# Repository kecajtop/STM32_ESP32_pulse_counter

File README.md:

# STM32_ESP32_pulse_counter

ESP32-S2-WROVER-I-N4R2

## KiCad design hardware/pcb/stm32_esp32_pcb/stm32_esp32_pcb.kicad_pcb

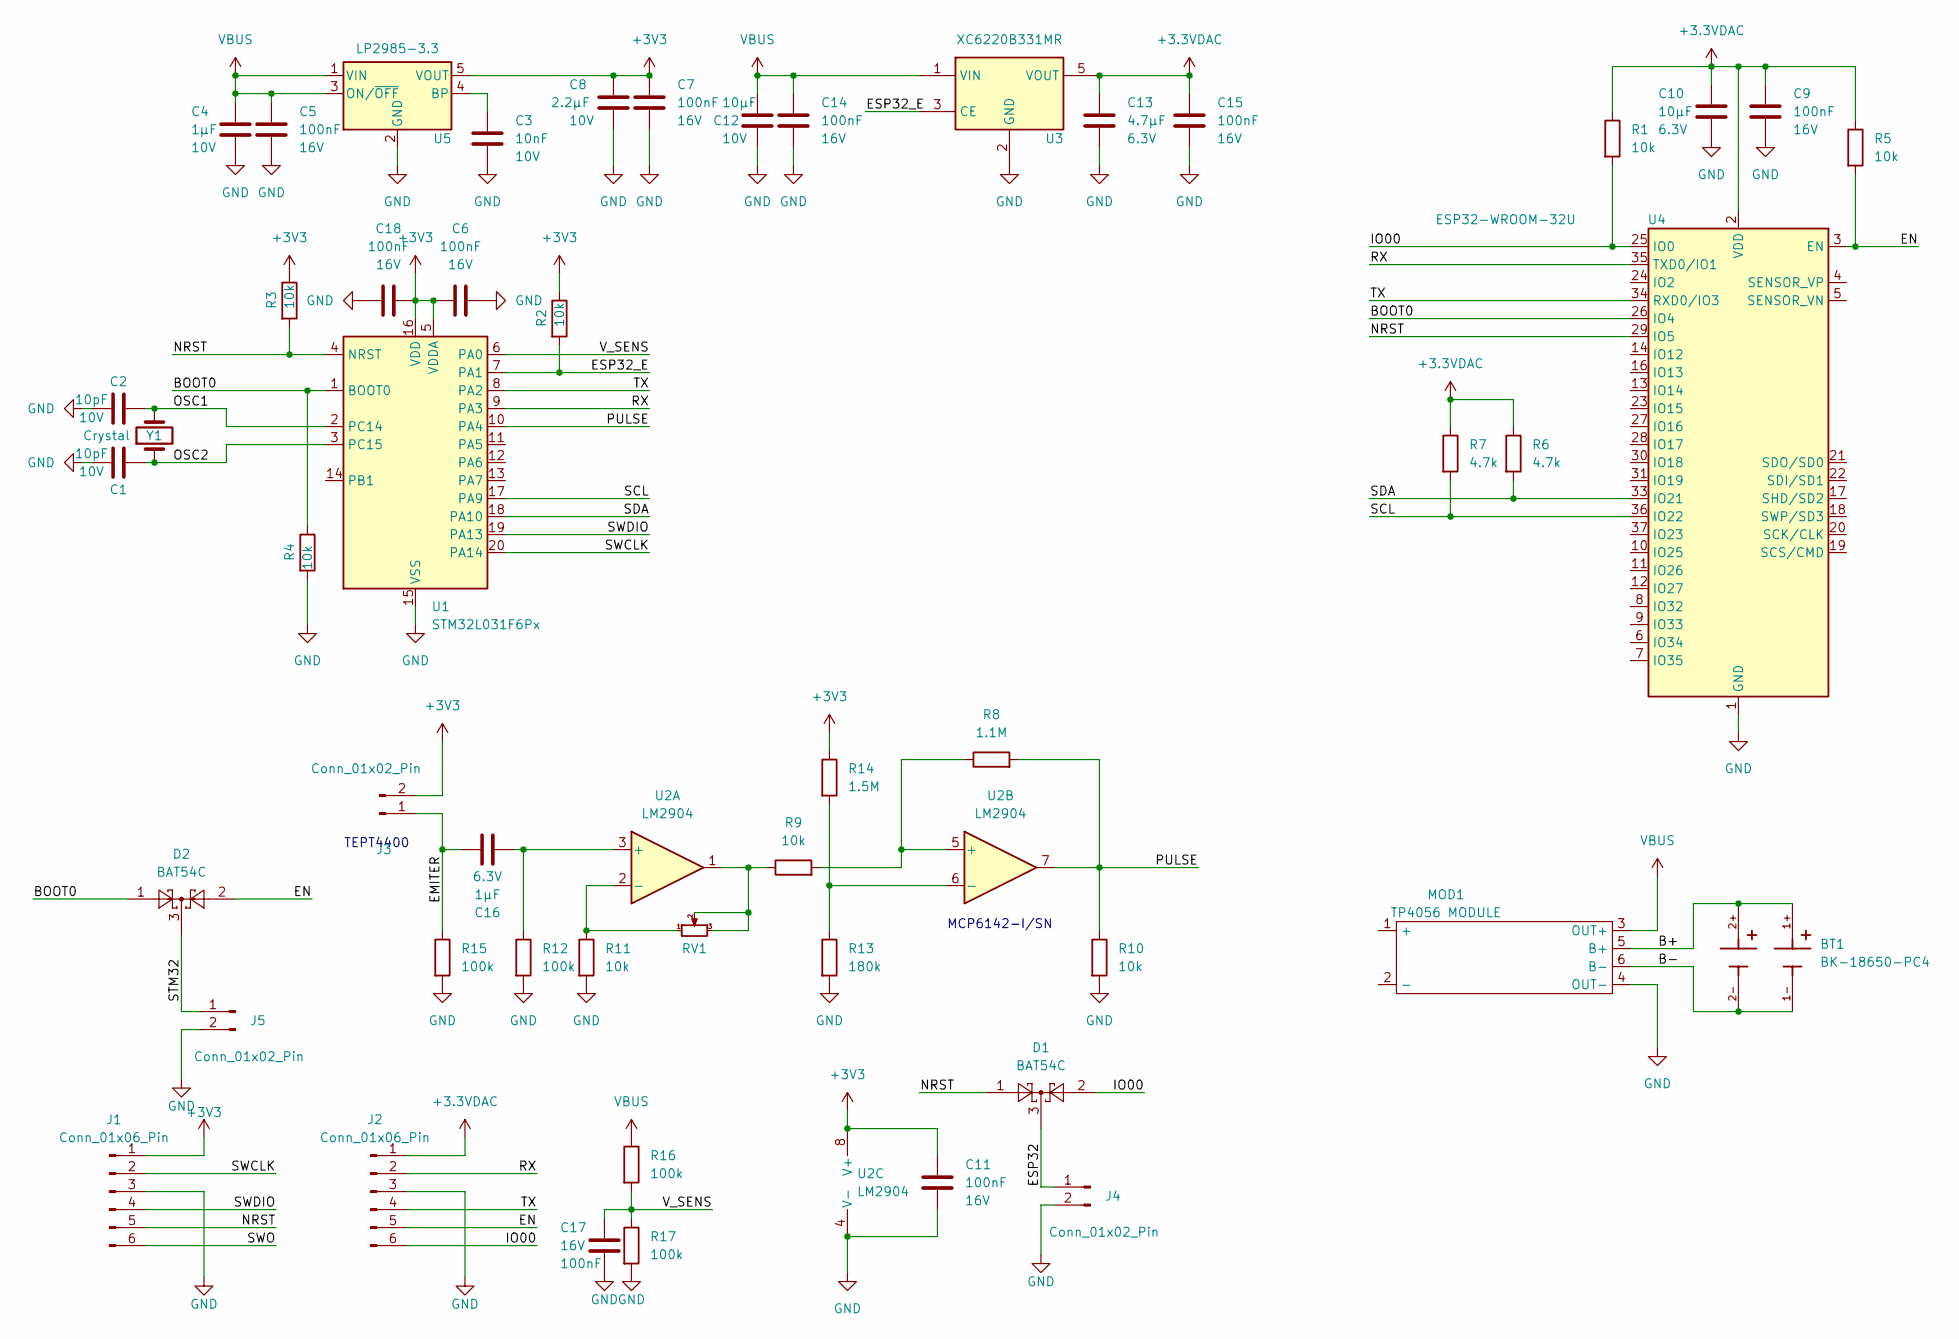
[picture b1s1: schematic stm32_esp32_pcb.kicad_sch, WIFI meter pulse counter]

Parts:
BT1: BK-18650-PC4; BAT_BK-18650-PC4; PARTREV K
C1, C2: C0603_10pF_10V_X7R; C_0603_1608Metric; Voltage 10V; Manufacturer Part Number C0603C100K8RAC7867
C3: C0603_10nF_10V_X7R; C_0603_1608Metric; Voltage 10V; Manufacturer Part Number C0603C103K8RACTU
C4: C0805_1µF_10V_X7R; C_0805_2012Metric; Voltage 10V; Manufacturer Part Number C0805C105K8RAC7025
C5, C6, C7, C9, C11, C14, C15, C17, C18: C0603_100nF_16V_X7R; C_0603_1608Metric; Voltage 16V; Manufacturer Part Number C0603C104J4RACTU
C8: C0603_2.2µF_10V_X7R; C_0603_1608Metric; Voltage 10V; Manufacturer Part Number C0603C225K8RACTU
C10: C0805_10µF_6.3V_X7R; C_0805_2012Metric; Voltage 6.3V; Manufacturer Part Number C0805C106K9RACTU
C12: C0805_10µF_10V_X7R; C_0805_2012Metric; Voltage 10V; Manufacturer Part Number C0805C106K8RACTU
C13: C0805_4.7µF_6.3V_X7R; C_0805_2012Metric; Voltage 6.3V; Manufacturer Part Number C0805C475K9RACTU
C16: C0603_1µF_6.3V_X7R; C_0603_1608Metric; Voltage 6.3V; Manufacturer Part Number C0603C105K9RACTU
D1, D2: BAT54C; SOT-23
J1, J2: Conn_01x06_Pin; PinHeader_1x06_P2.54mm_Horizontal
J3: Conn_01x02_Pin; PinHeader_1x02_P2.54mm_Horizontal
J4, J5: Conn_01x02_Pin; PinHeader_1x02_P2.54mm_Vertical
MOD1: TP4056 MODULE; TP4056-Module
R1, R2, R3, R4, R5, R9, R10, R11: R0603_10k_1%_100mW_100PPM_AC; R_0603_1608Metric; Manufacturer Part Number AC0603FR-0710KL
R6, R7: R0603_4.7k_1%_100mW_100PPM_AC; R_0603_1608Metric; Manufacturer Part Number AC0603FR-074K7L
R8: R0603_1.1M_1%_100mW_100PPM_RC; R_0603_1608Metric; Manufacturer Part Number RC0603FR-071M1L
R12, R15, R16, R17: R0603_100k_1%_100mW_100PPM_AC; R_0603_1608Metric; Manufacturer Part Number AC0603FR-07100KL
R13: R0603_180k_1%_100mW_100PPM_AC; R_0603_1608Metric; Manufacturer Part Number AC0603FR-07180KL
R14: R0603_1.5M_1%_100mW_100PPM_RC; R_0603_1608Metric; Manufacturer Part Number RC0603FR-071M5L
RV1: R_Potentiometer_Small; Potentiometer_Bourns_3266Y_Vertical
U1: STM32L031F6Px; TSSOP-20_4.4x6.5mm_P0.65mm
U2: LM2904; SOIC-8_3.9x4.9mm_P1.27mm
U3: XC6220B331MR; SOT-23-5
U4: ESP32-WROOM-32U
U5: LP2985-3.3; SOT-23-5
Y1: Crystal; Crystal_C38-LF_D3.0mm_L8.0mm_Horizontal_1EP_style1

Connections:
+3.3VDAC: C9.1, C10.1, C13.1, C15.1, J2.1, R1.1, R5.1, R6.1, R7.1, U3.5 (VOUT), U4.2 (VDD)
+3V3: C6.1, C7.1, C8.1, C11.1, C18.2, J1.1, J3.2, R2.1, R3.1, R14.1, U1.5 (VDDA), U1.16 (VDD), U2.8 (V+), U5.5 (VOUT)
/B+: BT1.1+, BT1.2+, MOD1.5 (B+)
/B-: BT1.1-, BT1.2-, MOD1.6 (B-)
/BOOT0: D2.1, R4.1, U1.1 (BOOT0), U4.26 (IO4)
/EMITER: C16.1, J3.1, R15.1
/EN: D2.2, J2.5, R5.2, U4.3 (EN)
/ESP32: D1.3, J4.1
/ESP32_E: R2.2, U1.7 (PA1), U3.3 (CE)
/IO00: D1.2, J2.6, R1.2, U4.25 (IO0)
/NRST: D1.1, J1.5, R3.2, U1.4 (NRST), U4.29 (IO5)
/OSC1: C2.2, U1.2 (PC14), Y1.2
/OSC2: C1.2, U1.3 (PC15), Y1.1
/PULSE: R8.2, R10.1, U1.10 (PA4), U2.7
/RX: J2.2, U1.9 (PA3), U4.35 (TXD0/IO1)
/SCL: R7.2, U1.17 (PA9), U4.36 (IO22)
/SDA: R6.2, U1.18 (PA10), U4.33 (IO21)
/STM32: D2.3, J5.1
/SWCLK: J1.2, U1.20 (PA14)
/SWDIO: J1.4, U1.19 (PA13)
/SWO: J1.6
/TX: J2.4, U1.8 (PA2), U4.34 (RXD0/IO3)
/V_SENS: C17.1, R16.2, R17.1, U1.6 (PA0)
GND: C1.1, C2.1, C3.2, C4.2, C5.2, C6.2, C7.2, C8.2, C9.2, C10.2, C11.2, C12.2, C13.2, C14.2, C15.2, C17.2, C18.1, J1.3, J2.3, J4.2, J5.2, MOD1.4 (OUT-), R4.2, R10.2, R11.2, R12.2, R13.2, R15.2, R17.2, U1.15 (VSS), U2.4 (V-), U3.2 (GND), U4.1 (GND), U4.15 (GND), U4.38 (GND), U4.39 (GND), U5.2 (GND)
unnamed: R9.1, RV1.2, RV1.3, U2.1
unnamed: C16.2, R12.1, U2.3 (+)
unnamed: R11.1, RV1.1, U2.2 (-)
unnamed: R8.1, R9.2, U2.5 (+)
unnamed: R13.1, R14.2, U2.6 (-)
unnamed: C3.1, U5.4 (BP)
VBUS: C4.1, C5.1, C12.1, C14.1, MOD1.3 (OUT+), R16.1, U3.1 (VIN), U5.1 (VIN), U5.3 (ON/~OFF)

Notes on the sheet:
MCP6142-I/SN
TEPT4400

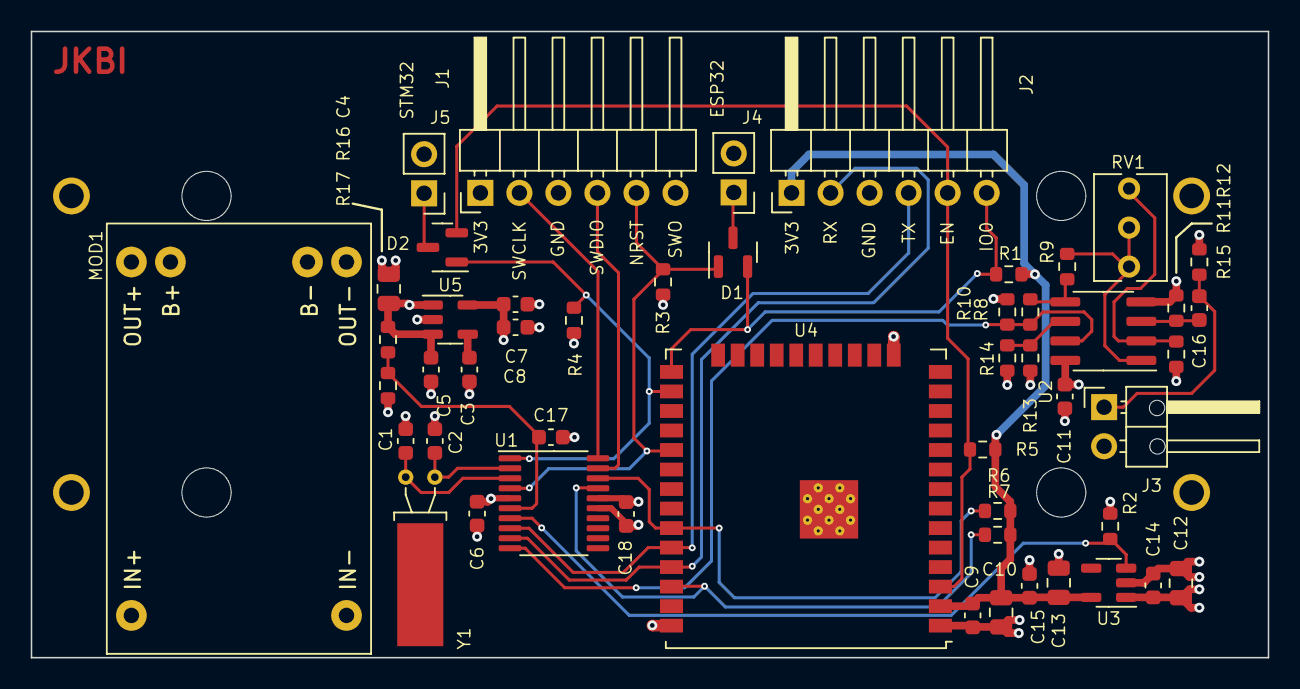
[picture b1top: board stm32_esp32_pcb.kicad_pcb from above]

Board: 4 copper layers, 80.5 x 40.8 mm, 51 parts (1 on the bottom side), 30 nets.

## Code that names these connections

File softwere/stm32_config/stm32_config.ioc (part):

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Mcu.Name=STM32L031F(4-6)Px
Mcu.Package=TSSOP20
Mcu.UserName=STM32L031F6Px
PA0-CK_IN.Mode=SYS_WakeUp0
PA0-CK_IN.Signal=SYS_WKUP1
PA1.Mode=IN1
PA1.Signal=ADC_IN1
PA10.Mode=I2C
PA10.Signal=I2C1_SDA
PA13.Mode=Serial_Wire
PA13.Signal=SYS_SWDIO
PA14.Mode=Serial_Wire
PA14.Signal=SYS_SWCLK
PA2.Mode=Asynchronous
PA2.Signal=LPUART1_TX
PA3.Mode=Asynchronous
PA3.Signal=LPUART1_RX
PA4.Mode=Counts_external_clock_with_synchro_01_occur1
PA4.Signal=LPTIM1_IN1
PA9.Mode=I2C
PA9.Signal=I2C1_SCL
PC14-OSC32_IN.Mode=LSE-External-Oscillator
PC14-OSC32_IN.Signal=RCC_OSC32_IN
PC15-OSC32_OUT.Mode=LSE-External-Oscillator
PC15-OSC32_OUT.Signal=RCC_OSC32_OUT
RCC.HSE_VALUE=8000000
RCC.SYSCLKFreq_VALUE=2097000
board=custom

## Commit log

2024-01-30 New documents added
2024-02-01 DRX check
    54 DRC errors left
2024-02-01 update
    Almos done
2024-02-01 DRC check
    11 DRC errors left
2024-02-02 New version
    Version 2 created
2024-02-02 update
    update
